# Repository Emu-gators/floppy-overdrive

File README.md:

# `floppy-overdrive`

## Overview

A revival of the floppy disk drive and controller for modern computers. _Sending floppies into overdrive!_

## Organization

The project is laid out with the following directories:

- `docs`: relevant project documentation and research resources
- `hw`: HDL code and testbenches
- `pcb` : KiCad project for the control circuit PCB
- `pcb_tests` : Test code and procedures for the control circuit PCB
- `sw`: software code and scripts

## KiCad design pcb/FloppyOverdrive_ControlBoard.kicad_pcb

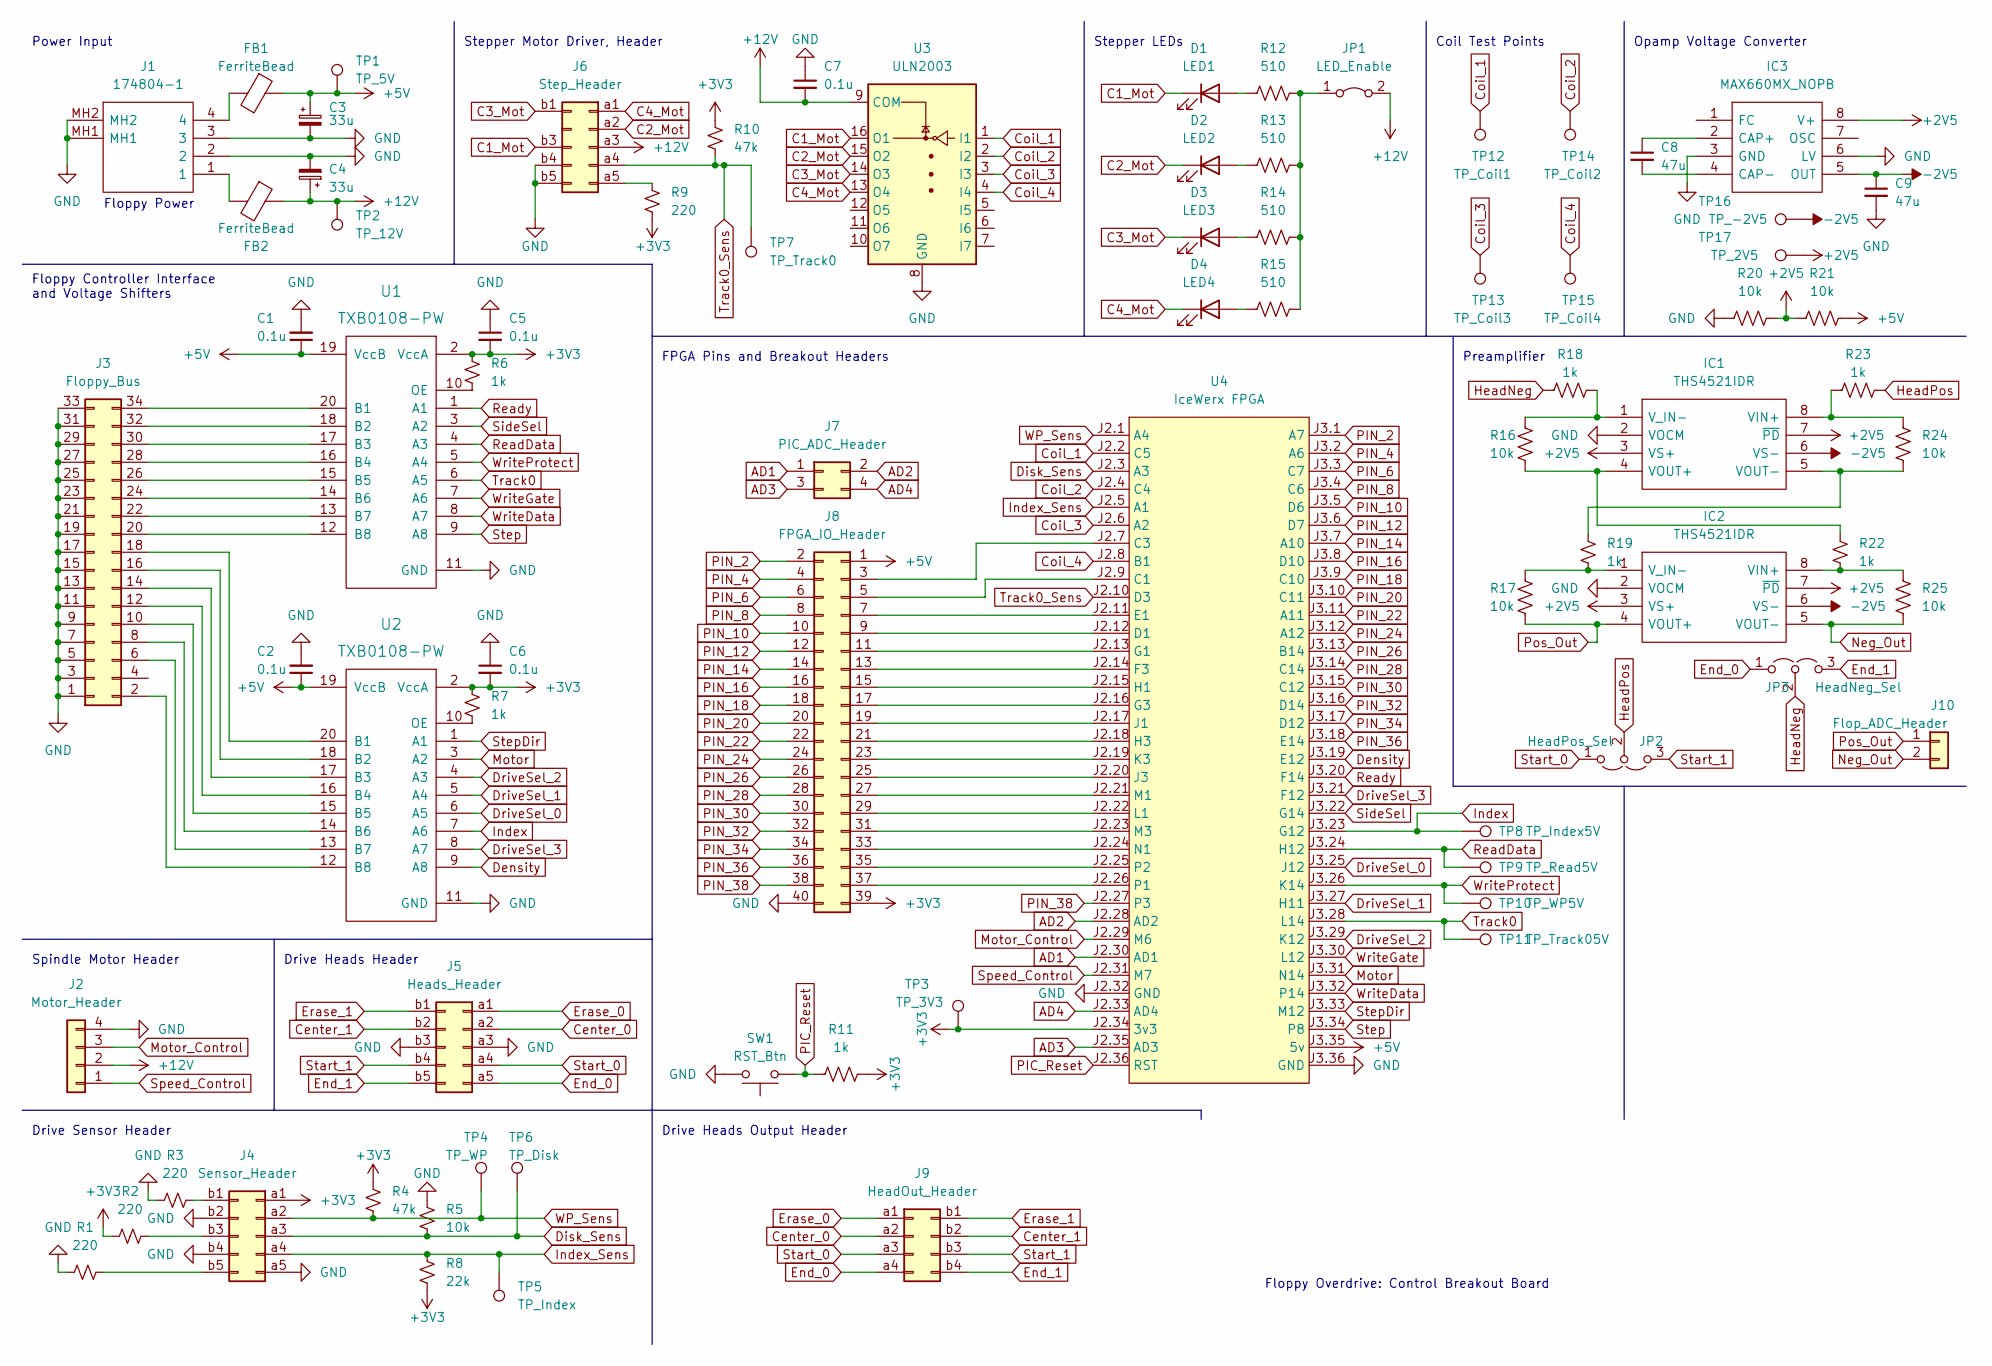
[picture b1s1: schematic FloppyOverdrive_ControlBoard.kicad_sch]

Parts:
C1, C2, C5, C6, C7: 0.1u; C_Disc_D5.0mm_W2.5mm_P2.50mm
C3, C4: 33u; CP_Radial_D5.0mm_P2.00mm
C8, C9: 47u; C_Disc_D5.0mm_W2.5mm_P2.50mm
D1: LED1; LED_D5.0mm
D2: LED2; LED_D5.0mm
D3: LED3; LED_D5.0mm
D4: LED4; LED_D5.0mm
FB1, FB2: FerriteBead; R_1206_3216Metric
IC1, IC2: THS4521IDR; SOIC127P600X175-8N; Mouser Part Number 595-THS4521IDR
IC3: MAX660MX_NOPB; SOIC127P600X175-8N; Mouser Part Number 926-MAX660MX/NOPB
J1: 174804-1; 1748041; Manufacturer_Part_Number 174804-1; Mouser Part Number 571-1748041
J2: Motor_Header; SHDRRA4W50P15X200_1X4_1000X770X525P
J3: Floppy_Bus; PinHeader_2x17_P2.54mm_Vertical
J4: Sensor_Header; PinHeader_2x05_P2.54mm_Horizontal
J5: Heads_Header; PinHeader_2x05_P2.54mm_Horizontal
J6: Step_Header; PinHeader_2x05_P2.00mm_Horizontal
J7: PIC_ADC_Header; PinHeader_2x02_P2.54mm_Vertical
J8: FPGA_IO_Header; PinHeader_2x20_P2.54mm_Vertical
J9: HeadOut_Header; PinHeader_2x04_P2.54mm_Vertical
J10: Flop_ADC_Header; PinHeader_1x02_P2.54mm_Vertical
JP1: LED_Enable; PinHeader_1x02_P2.54mm_Vertical
JP2: HeadPos_Sel; PinHeader_1x03_P2.54mm_Vertical
JP3: HeadNeg_Sel; PinHeader_1x03_P2.54mm_Vertical
R1, R2, R3, R9: 220; R_Axial_DIN0207_L6.3mm_D2.5mm_P10.16mm_Horizontal
R4, R10: 47k; R_Axial_DIN0207_L6.3mm_D2.5mm_P10.16mm_Horizontal
R5: 10k; R_Axial_DIN0207_L6.3mm_D2.5mm_P10.16mm_Horizontal
R6, R7, R11: 1k; R_Axial_DIN0207_L6.3mm_D2.5mm_P10.16mm_Horizontal
R8: 22k; R_Axial_DIN0207_L6.3mm_D2.5mm_P10.16mm_Horizontal
R12, R13, R14, R15: 510; R_Axial_DIN0207_L6.3mm_D2.5mm_P10.16mm_Horizontal
R16, R17, R20, R21, R24, R25: 10k; R_0402_1005Metric
R18, R19, R22, R23: 1k; R_0402_1005Metric
SW1: RST_Btn; SW_PUSH_6mm
TP1: TP_5V; TestPoint_Pad_D1.0mm
TP2: TP_12V; TestPoint_Pad_D1.0mm
TP3: TP_3V3; TestPoint_Pad_D1.0mm
TP4: TP_WP; TestPoint_Pad_D1.0mm
TP5: TP_Index; TestPoint_Pad_D1.0mm
TP6: TP_Disk; TestPoint_Pad_D1.0mm
TP7: TP_Track0; TestPoint_Pad_D1.0mm
TP8: TP_Index5V; TestPoint_Pad_D1.0mm
TP9: TP_Read5V; TestPoint_Pad_D1.0mm
TP10: TP_WP5V; TestPoint_Pad_D1.0mm
TP11: TP_Track05V; TestPoint_Pad_D1.0mm
TP12: TP_Coil1; TestPoint_Pad_D1.0mm
TP13: TP_Coil3; TestPoint_Pad_D1.0mm
TP14: TP_Coil2; TestPoint_Pad_D1.0mm
TP15: TP_Coil4; TestPoint_Pad_D1.0mm
TP16: TP_-2V5; TestPoint_Pad_D1.0mm
TP17: TP_2V5; TestPoint_Pad_D1.0mm
U1, U2: TXB0108-PW; TSSOP-20_4.4x6.5mm_P0.65mm
U3: ULN2003; TSSOP-16_4.4x5mm_P0.65mm
U4: IceWerx FPGA

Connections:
+2V5: IC1.3 (VS+), IC1.7 (~PD), IC2.3 (VS+), IC2.7 (~PD), IC3.8 (V+), R20.2, R21.1, TP17.1
+3V3: C5.2, C6.2, J4.a1, J8.39, R2.1, R4.1, R6.1, R7.1, R8.2, R9.2, R10.1, R11.2, TP3.1, U1.2 (VccA), U2.2 (VccA), U4.J2.34 (3v3)
+5V: C1.1, C2.1, C3.1, FB1.1, J8.1, R21.2, TP1.1, U1.19 (VccB), U2.19 (VccB), U4.J3.35 (5v)
+12V: C4.1, C7.2, FB2.1, J2.2, J6.a3, JP1.2 (B), TP2.1, U3.9 (COM)
-2V5: C9.1, IC1.6 (VS-), IC2.6 (VS-), IC3.5 (OUT), TP16.1
AD1: J7.1, U4.J2.30 (AD1)
AD2: J7.2, U4.J2.28 (AD2)
AD3: J7.3, U4.J2.35 (AD3)
AD4: J7.4, U4.J2.33 (AD4)
C1_Mot: D1.1 (K), J6.b3, U3.16 (O1)
C2_Mot: D2.1 (K), J6.a2, U3.15 (O2)
C3_Mot: D3.1 (K), J6.b1, U3.14 (O3)
C4_Mot: D4.1 (K), J6.a1, U3.13 (O4)
Center_0: J5.a2, J9.a2
Center_1: J5.b2, J9.b2
Coil_1: TP12.1, U3.1 (I1), U4.J2.2 (C5)
Coil_2: TP14.1, U3.2 (I2), U4.J2.4 (C4)
Coil_3: TP13.1, U3.3 (I3), U4.J2.6 (A2)
Coil_4: TP15.1, U3.4 (I4), U4.J2.8 (B1)
Density: U2.9 (A8), U4.J3.19 (E12)
Disk_Sens: J4.a3, R5.2, TP6.1, U4.J2.3 (A3)
DriveSel_0: U2.6 (A5), U4.J3.25 (J12)
DriveSel_1: U2.5 (A4), U4.J3.27 (H11)
DriveSel_2: U2.4 (A3), U4.J3.29 (K12)
DriveSel_3: U2.8 (A7), U4.J3.21 (F12)
End_0: J5.a5, J9.a4, JP3.1 (A)
End_1: J5.b5, J9.b4, JP3.3 (B)
Erase_0: J5.a1, J9.a1
Erase_1: J5.b1, J9.b1
GND: C1.2, C2.2, C3.2, C4.2, C5.1, C6.1, C7.1, C9.2, IC1.2 (VOCM), IC2.2 (VOCM), IC3.3 (GND), IC3.6 (LV), J1.2, J1.3, J1.MH1, J1.MH2, J2.4, J3.1, J3.3, J3.5, J3.7, J3.9, J3.11, J3.13, J3.15, J3.17, J3.19, J3.21, J3.23, J3.25, J3.27, J3.29, J3.31, J3.33, J4.a5, J4.b2, J4.b4, J5.a3, J5.b3, J6.b4, J6.b5, J8.40, R1.1, R3.1, R5.1, R20.1, SW1.2, U1.11 (GND), U2.11 (GND), U3.8 (GND), U4.J2.32 (GND), U4.J3.36 (GND)
HeadNeg: JP3.2 (C), R18.1
HeadPos: JP2.2 (C), R23.2
Index: TP8.1, U2.7 (A6), U4.J3.23 (G12)
Index_Sens: J4.a4, R8.1, TP5.1, U4.J2.5 (A1)
Motor: U2.3 (A2), U4.J3.31 (N14)
Motor_Control: J2.3, U4.J2.29 (M6)
Neg_Out: IC2.5 (VOUT-), J10.2, R25.2
unnamed: C8.1, IC3.2 (CAP+)
unnamed: C8.2, IC3.4 (CAP-)
unnamed: D1.2 (A), R12.1
unnamed: D2.2 (A), R13.1
unnamed: D3.2 (A), R14.1
unnamed: D4.2 (A), R15.1
unnamed: FB1.2, J1.4
unnamed: FB2.2, J1.1
unnamed: IC1.1 (V_IN-), R16.1, R18.2
unnamed: IC1.4 (VOUT+), R16.2, R22.1
unnamed: IC1.5 (VOUT-), R19.1, R24.2
unnamed: IC1.8 (VIN+), R23.1, R24.1
unnamed: IC2.1 (V_IN-), R17.1, R19.2
unnamed: IC2.8 (VIN+), R22.2, R25.1
unnamed: J3.2, U2.12 (B8)
unnamed: J3.6, U2.13 (B7)
unnamed: J3.8, U2.14 (B6)
unnamed: J3.10, U2.15 (B5)
unnamed: J3.12, U2.16 (B4)
unnamed: J3.14, U2.17 (B3)
unnamed: J3.16, U2.18 (B2)
unnamed: J3.18, U2.20 (B1)
unnamed: J3.20, U1.12 (B8)
unnamed: J3.22, U1.13 (B7)
unnamed: J3.24, U1.14 (B6)
unnamed: J3.26, U1.15 (B5)
unnamed: J3.28, U1.16 (B4)
unnamed: J3.30, U1.17 (B3)
unnamed: J3.32, U1.18 (B2)
unnamed: J3.34, U1.20 (B1)
unnamed: J4.b1, R3.2
unnamed: J4.b3, R2.2
unnamed: J4.b5, R1.2
unnamed: J6.a5, R9.1
unnamed: J8.3, U4.J2.7 (C3)
unnamed: J8.5, U4.J2.9 (C1)
unnamed: J8.7, U4.J2.11 (E1)
unnamed: J8.9, U4.J2.12 (D1)
unnamed: J8.11, U4.J2.13 (G1)
unnamed: J8.13, U4.J2.14 (F3)
unnamed: J8.15, U4.J2.15 (H1)
unnamed: J8.17, U4.J2.16 (G3)
unnamed: J8.19, U4.J2.17 (J1)
unnamed: J8.21, U4.J2.18 (H3)
unnamed: J8.23, U4.J2.19 (K3)
unnamed: J8.25, U4.J2.20 (J3)
unnamed: J8.27, U4.J2.21 (M1)
unnamed: J8.29, U4.J2.22 (L1)
unnamed: J8.31, U4.J2.23 (M3)
unnamed: J8.33, U4.J2.24 (N1)
unnamed: J8.35, U4.J2.25 (P2)
unnamed: J8.37, U4.J2.26 (P1)
unnamed: JP1.1 (A), R12.2, R13.2, R14.2, R15.2
unnamed: R6.2, U1.10 (OE)
unnamed: R7.2, U2.10 (OE)
PIC_Reset: R11.1, SW1.1, U4.J2.36 (RST)
PIN_2: J8.2, U4.J3.1 (A7)
PIN_4: J8.4, U4.J3.2 (A6)
PIN_6: J8.6, U4.J3.3 (C7)
PIN_8: J8.8, U4.J3.4 (C6)
PIN_10: J8.10, U4.J3.5 (D6)
PIN_12: J8.12, U4.J3.6 (D7)
PIN_14: J8.14, U4.J3.7 (A10)
PIN_16: J8.16, U4.J3.8 (D10)
PIN_18: J8.18, U4.J3.9 (C10)
PIN_20: J8.20, U4.J3.10 (C11)
PIN_22: J8.22, U4.J3.11 (A11)
PIN_24: J8.24, U4.J3.12 (A12)
PIN_26: J8.26, U4.J3.13 (B14)
PIN_28: J8.28, U4.J3.14 (C14)
PIN_30: J8.30, U4.J3.15 (C12)
PIN_32: J8.32, U4.J3.16 (D14)
PIN_34: J8.34, U4.J3.17 (D12)
PIN_36: J8.36, U4.J3.18 (E14)
PIN_38: J8.38, U4.J2.27 (P3)
Pos_Out: IC2.4 (VOUT+), J10.1, R17.2
ReadData: TP9.1, U1.4 (A3), U4.J3.24 (H12)
Ready: U1.1 (A1), U4.J3.20 (F14)
SideSel: U1.3 (A2), U4.J3.22 (G14)
Speed_Control: J2.1, U4.J2.31 (M7)
Start_0: J5.a4, J9.a3, JP2.1 (A)
Start_1: J5.b4, J9.b3, JP2.3 (B)
Step: U1.9 (A8), U4.J3.34 (P8)
StepDir: U2.1 (A1), U4.J3.33 (M12)
Track0: TP11.1, U1.6 (A5), U4.J3.28 (L14)
Track0_Sens: J6.a4, R10.2, TP7.1, U4.J2.10 (D3)
WP_Sens: J4.a2, R4.2, TP4.1, U4.J2.1 (A4)
WriteData: U1.8 (A7), U4.J3.32 (P14)
WriteGate: U1.7 (A6), U4.J3.30 (L12)
WriteProtect: TP10.1, U1.5 (A4), U4.J3.26 (K14)

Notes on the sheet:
FPGA Pins and Breakout Headers
Drive Sensor Header
Spindle Motor Header
Floppy Controller Interface and Voltage Shifters
Stepper Motor Driver, Header
Preamplifier
Drive Heads Header
Stepper LEDs
Floppy Overdrive: Control Breakout Board
Floppy Power
Coil Test Points
Opamp Voltage Converter
Drive Heads Output Header
Power Input

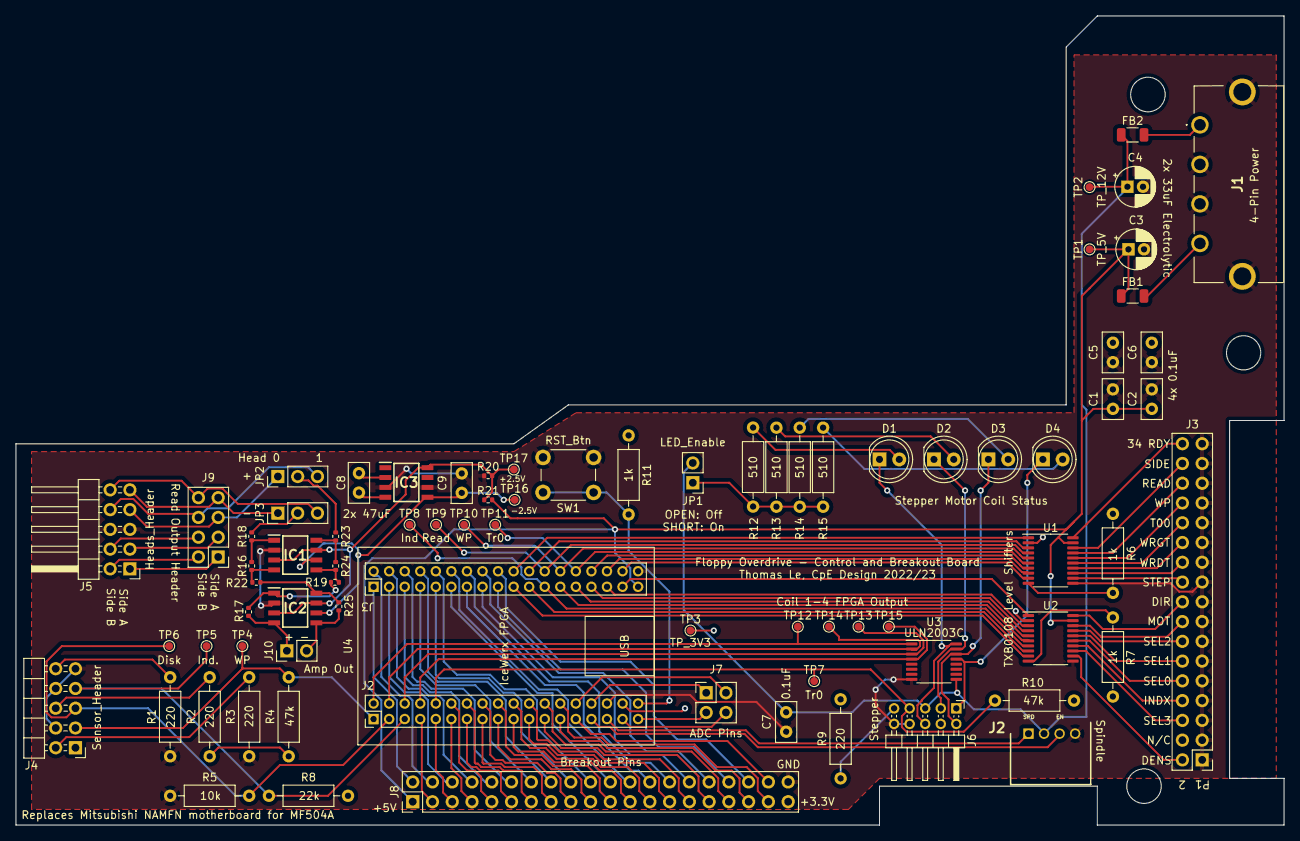
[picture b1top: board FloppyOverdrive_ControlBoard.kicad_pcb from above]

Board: 2 copper layers, 163.0 x 104.0 mm, 78 parts (0 on the bottom side), 127 nets.

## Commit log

2022-10-23 organizes project and adds research links
2022-11-01 Created bare top-level entity
2022-11-01 adds controller circuit interface
2022-11-01 adjusts misc. syntax things
2022-11-01 fixes typos
2022-11-01 adds read/write circuit interface
2022-11-01 removes hidden .gitkeep file
2022-11-01 fixes commented-out misspelled wire name
2022-11-17 Added controller test harness + implementation
2023-01-03 Modified to account for active-low logic
2023-01-20 Rewrote step driver to add debounce
2023-01-26 Added schematics for test circuits
2023-01-27 Added README to /hw
2023-02-05 Updated debounce for and ctrl_circ logic
2023-02-05 Added ctrl_circ testbench
2023-02-14 Added pcb files
2023-02-14 Extended debounce to improve step behavior
2023-02-14 Add motor header files, outline for PCB
2023-02-16 Added LEDs, footprints to PCB schematic
2023-02-17 PCB Update
2023-02-17 Clarified testbench
2023-02-18 Updated READMEs
2023-02-18 Added ADC files
2023-02-18 Worked on PCB layout, began adding test points
2023-02-18 Sync commit
2023-02-20 Routing first draft
2023-02-21 Fixed incorrect routing, added silkscreen info
2023-02-21 Fixed floppy bus orientation
2023-02-22 Added PCB test points, fixed schematic
2023-02-22 Sync backups
2023-02-23 Backup sync
2023-02-26 Verified JLCPCB DRC
2023-02-27 Adjusted screw holes
2023-02-27 Generated BOM
2023-03-02 Test commit
2023-03-02 Removed test file
2023-03-02 Added neg voltage and amps
2023-03-03 Generated gerbers
2023-03-06 Updated BOM
2023-03-21 Added bus tests
2023-03-23 Added sensor tests
2023-03-23 Added motor tests
2023-03-23 Modified pcb_tests README
2023-03-23 Added test procedures
2023-03-23 Fixed pin 39, added missing hole to PCB
2023-03-23 Bugfixes for pcb tests
2023-03-23 Corrected test test_procedures
2023-03-23 Added to main README
2023-03-23 Fixed a typo
2023-03-25 Elaborated test procedures
2023-03-29 Added automatic step test and pll to step_manual
2023-03-29 Added bus pinout to silkscreen
2023-04-02 Code cleanup, add build for ctrl_board
2023-04-03 Control circuit bugfixes
2023-04-05 Began updating docs
2023-04-06 Added spin info to silkscreen
2023-04-07 Added project documentation
2023-04-07 Fixed doc formatting
